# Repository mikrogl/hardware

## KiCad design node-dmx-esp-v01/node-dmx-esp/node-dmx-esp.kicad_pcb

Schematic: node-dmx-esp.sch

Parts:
C2: 22uF; CP_Elec_4x4.5
C3, C4: 100nF; C_0805_2012Metric
C5: 47uF; CP_Elec_4x4.5
D1, D2: LED; LED_0805_2012Metric
J1: Conn_01x03_Female; PinHeader_1x03_P2.54mm_Vertical
J2, J3: Conn_01x02_Female; PinHeader_1x02_P2.54mm_Vertical
R1, R3: 560; R_0603_1608Metric
R2, R5: 1k; R_0603_1608Metric
R4: 130; R_0603_1608Metric
R6, R7: R; R_0603_1608Metric
SW1, SW2: SW_Push; SW_SPST_EVQPE1
U1: AMS1117-3.3; SOT-223-3_TabPin2
U2: MAX485E; SOIC-8_3.9x4.9mm_P1.27mm
U3: ESP-12E; ESP-12E_SMD

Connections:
+3V3: C4.1, C5.1, R2.1, R5.1, U1.2 (VO), U3.3, U3.8
+5V: C2.1, C3.1, J3.1, R1.1, U1.3 (VI), U2.8 (VCC)
D_EN: U2.2 (~RE), U2.3 (DE), U3.14
Flash: R2.2, U3.12; also elsewhere on the board
GND: C2.2, C3.2, C4.2, C5.2, D1.1, D2.1, J1.1, J3.2, R3.2, U1.1 (GND), U2.5 (GND), U3.9; also elsewhere on the board
LEDA: R6.2, U3.5
LEDB: R7.1, U3.6
unnamed: D1.2, R6.1
unnamed: D2.2, R7.2
unnamed: J1.2, R1.2, R4.1, U2.6 (A)
unnamed: J1.3, R3.1, R4.2, U2.7 (B)
RX: J2.2, U2.1 (RO), U3.15
Reset: R5.2, U3.1; also elsewhere on the board
TX: J2.1, U2.4 (DI), U3.16

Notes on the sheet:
MAX485
Voltage Regulator

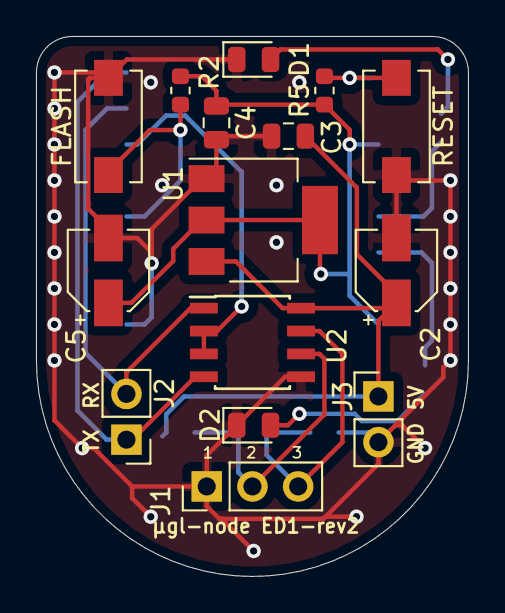
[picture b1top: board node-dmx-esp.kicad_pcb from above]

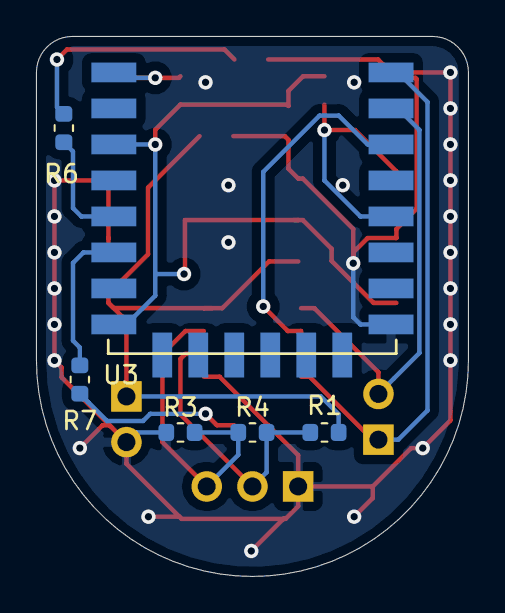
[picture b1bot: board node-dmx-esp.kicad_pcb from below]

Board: 2 copper layers, 24.0 x 30.0 mm, 21 parts (6 on the bottom side), 14 nets.

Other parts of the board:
FLASH: SW_Push; SW_SPST_EVQPE1
RESET: SW_Push; SW_SPST_EVQPE1

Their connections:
Flash: FLASH.2; also elsewhere on the board
GND: FLASH.1, RESET.1; also elsewhere on the board
Reset: RESET.2; also elsewhere on the board

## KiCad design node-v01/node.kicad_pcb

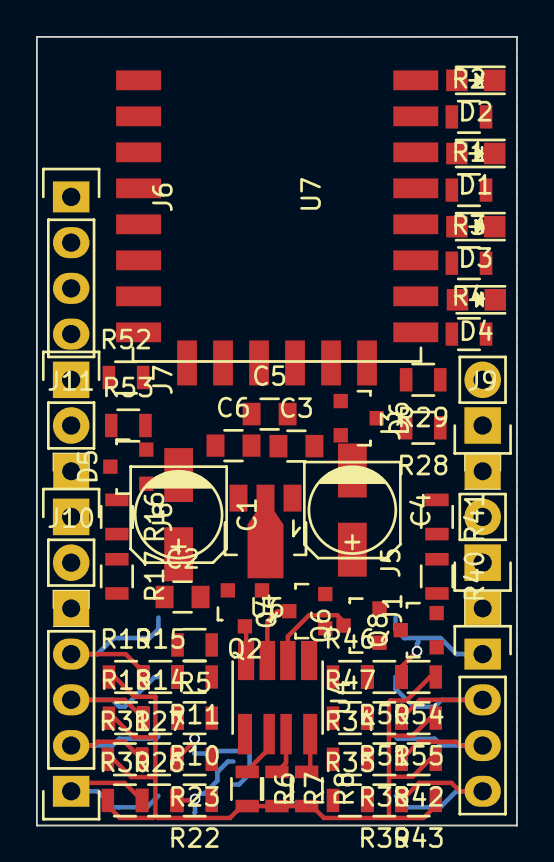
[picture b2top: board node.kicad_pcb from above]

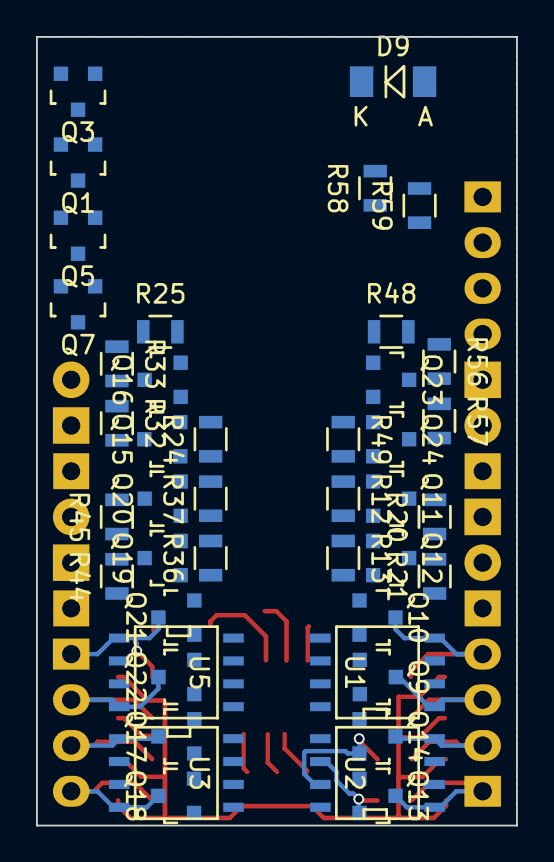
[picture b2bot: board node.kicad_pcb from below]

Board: 4 copper layers, 26.7 x 43.8 mm, 113 parts (43 on the bottom side), 57 nets.

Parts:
C1: CP; c_elec_5x4.5
C2, C3, C5, C6: C; C_0805
C4: CP; c_elec_5x5.3
D1, D2, D3, D4: LED; LED_0805
D5, D6: BAT54A; SOT-23
D9: D_Zener; MiniMELF_Standard
J1, J9, J10, J11: Conn_01x01; Pin_Header_Straight_1x01
J2, J4, J6: Conn_01x04; Socket_Strip_Straight_1x04
J3, J5, J7, J8: Conn_01x02; Socket_Strip_Straight_1x02
Q1, Q2, Q3, Q4, Q5, Q6, Q7, Q8, Q9, Q10, Q11, Q12, Q13, Q14, Q15, Q16, Q17, Q18, Q19, Q20, Q21, Q22, Q23, Q24: 2N7002; SOT-23
R1, R2, R3, R4, R5, R6, R7, R8, R10, R11, R12, R13, R14, R15, R16, R17, R18, R19, R20, R21, R22, R23, R24, R25, R26, R27, R28, R29, R30, R31, R32, R33, R34, R35, R36, R37, R38, R39, R40, R41, R42, R43, R44, R45, R46, R47, R48, R49, R50, R51, R52, R53, R54, R55, R56, R57, R58, R59: R; R_0805
U1, U2, U3, U5: L9110S; SOIC-8-N
U4: CLQ6A-TKW; PLCC8
U6: 78L03CX; SOT89-3_Housing
U7: RTL8710

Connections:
+3V3: C3.1, C4.1, D6.3, D9.1, J1.1, Q9.1, Q10.1, Q11.1, Q12.1, Q13.1, Q14.1, Q15.1, Q16.1, Q17.1, Q18.1, Q19.1, Q20.1, Q21.1, Q22.1, Q23.1, Q24.1, R10.1, R11.1, R12.1, R13.1, R22.1, R23.1, R24.1, R25.1, R34.1, R35.1, R36.1, R37.1, R46.1, R47.1, R48.1, R49.1, R58.1, U6.1, U7.8
EN_CH: R58.2, U7.3
GND: C1.2, C2.2, C3.2, C4.2, C5.2, C6.2, D9.2, J6.2, J9.1, J10.1, Q1.2, Q2.2, Q3.2, Q4.2, Q5.2, Q6.2, Q7.2, Q8.2, R59.1, U1.5, U1.8, U2.5, U2.8, U3.5, U3.8, U5.5, U5.8, U6.3, U7.15
GPIO4: J2.1, Q13.3, R26.1, R30.2, U2.1
GPIO5: J2.2, Q14.3, R27.1, R31.2, U2.4
GPIO6: J2.3, Q9.3, R14.1, R18.2, U1.1
GPIO7: J2.4, Q10.3, R15.1, R19.2, U1.4
IGPIO4: Q1.1, Q13.2, R22.2, R26.2, U2.6, U7.5
IGPIO5: Q3.1, Q14.2, R23.2, R27.2, U2.7, U7.9
IGPIO6: Q5.1, Q9.2, R10.2, R14.2, U1.6, U7.11
IGPIO7: Q7.1, Q10.2, R11.2, R15.2, U1.7, U7.14
IPWM0: Q2.1, Q21.2, R46.2, R50.2, U5.6, U7.18
IPWM1: Q4.1, Q22.2, R47.2, R51.2, U5.7, U7.20
IPWM2: Q6.1, Q17.2, R34.2, R38.2, U3.6, U7.1
IPWM3: Q8.1, Q18.2, R35.2, R39.2, U3.7, U7.19
ISPI0: Q11.2, R12.2, R16.2, U7.7
ISPI1: Q12.2, R13.2, R17.2, U7.12
I_RX0: Q15.2, R24.2, R28.2, U7.22
I_RX1: Q19.2, R36.2, R40.2, U7.13
I_SCL: Q24.2, R49.2, R53.2, U7.2
I_SDA: Q23.2, R48.2, R52.2, U7.10
I_TX0: Q16.2, R25.2, R29.2, U7.21
I_TX1: Q20.2, R37.2, R41.2, U7.17
LC0: Q2.3, U4.8
LC1: Q4.3, U4.7
LC2: Q6.3, U4.6
LC3: Q8.3, U4.5
unnamed: C1.1, C2.1, D5.1, D6.1, U6.2
unnamed: D1.1, Q1.3
unnamed: D1.2, R1.1
unnamed: D2.1, Q3.3
unnamed: D2.2, R2.1
unnamed: D3.1, Q5.3
unnamed: D3.2, R3.1
unnamed: D4.1, Q7.3
unnamed: D4.2, R4.1
unnamed: R5.1, U4.1
unnamed: R6.1, U4.2
unnamed: R7.1, U4.3
unnamed: R8.1, U4.4
PWM0: J4.1, Q21.3, R50.1, R54.2, U5.1
PWM1: J4.2, Q22.3, R51.1, R55.2, U5.4
PWM2: J4.3, Q17.3, R38.1, R42.2, U3.1
PWM3: J4.4, Q18.3, R39.1, R43.2, U3.4
RESET: J6.4, U7.16
RX0: J3.1, Q15.3, R28.1, R32.2
RX1: J5.1, Q19.3, R40.1, R44.2
SCL: J7.2, Q24.3, R53.1, R57.2
SDA: J7.1, Q23.3, R52.1, R56.2
SPI0: J8.1, Q11.3, R16.1, R20.2
SPI1: J8.2, Q12.3, R17.1, R21.2
SWCLK: J6.1, U7.4
SWDIO: J6.3, U7.6
TX0: J3.2, Q16.3, R29.1, R33.2
TX1: J5.2, Q20.3, R41.1, R45.2
VDD: C6.1, D5.2, D6.2, R1.2, R2.2, R3.2, R4.2, R5.2, R6.2, R7.2, R8.2, R18.1, R19.1, R20.1, R21.1, R30.1, R31.1, R32.1, R33.1, R42.1, R43.1, R44.1, R45.1, R54.1, R55.1, R56.1, R57.1, U1.2, U1.3, U2.2, U2.3, U3.2, U3.3, U5.2, U5.3
VIN: C5.1, D5.3, J11.1

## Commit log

2018-05-15 node v1
2018-09-22 node-dmx-esp rev2
